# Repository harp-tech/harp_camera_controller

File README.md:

# Harp Camera Controlelr

This device contains the necessary circuitry to synchronously control and supply 2 cameras.

# Licensing

The code, designs, documentation, and photos available in this repository is free: you can redistribute it and/or modify it under the terms of the used license.
Each subdirectory will contain a license or, possibly, a set of licenses if it involves both hardware and software. Check files named LICENSE.

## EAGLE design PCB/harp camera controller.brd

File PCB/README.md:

# Harp Camera Controller

## Licensing

The designs, documentation, and photos available in this repository are free: you can redistribute it and/or modify it under the terms of the used license.
Check file named LICENSE.

Copyright OEPS 2021-2022

<br />This work is licensed under a <a rel="license" href="http://creativecommons.org/licenses/by-nc-sa/3.0/igo/">Creative Commons Attribution-NonCommercial-ShareAlike 3.0 IGO License</a>.

If your are interested in obtaining a license to sell this device, please contact info@oeps.tech

[1]: https://docs.google.com/spreadsheets/d/1aobmmEzBDethzIlrm1eg0eYkBqlyX3s9WbA9KgRwVQI/edit?usp=sharing

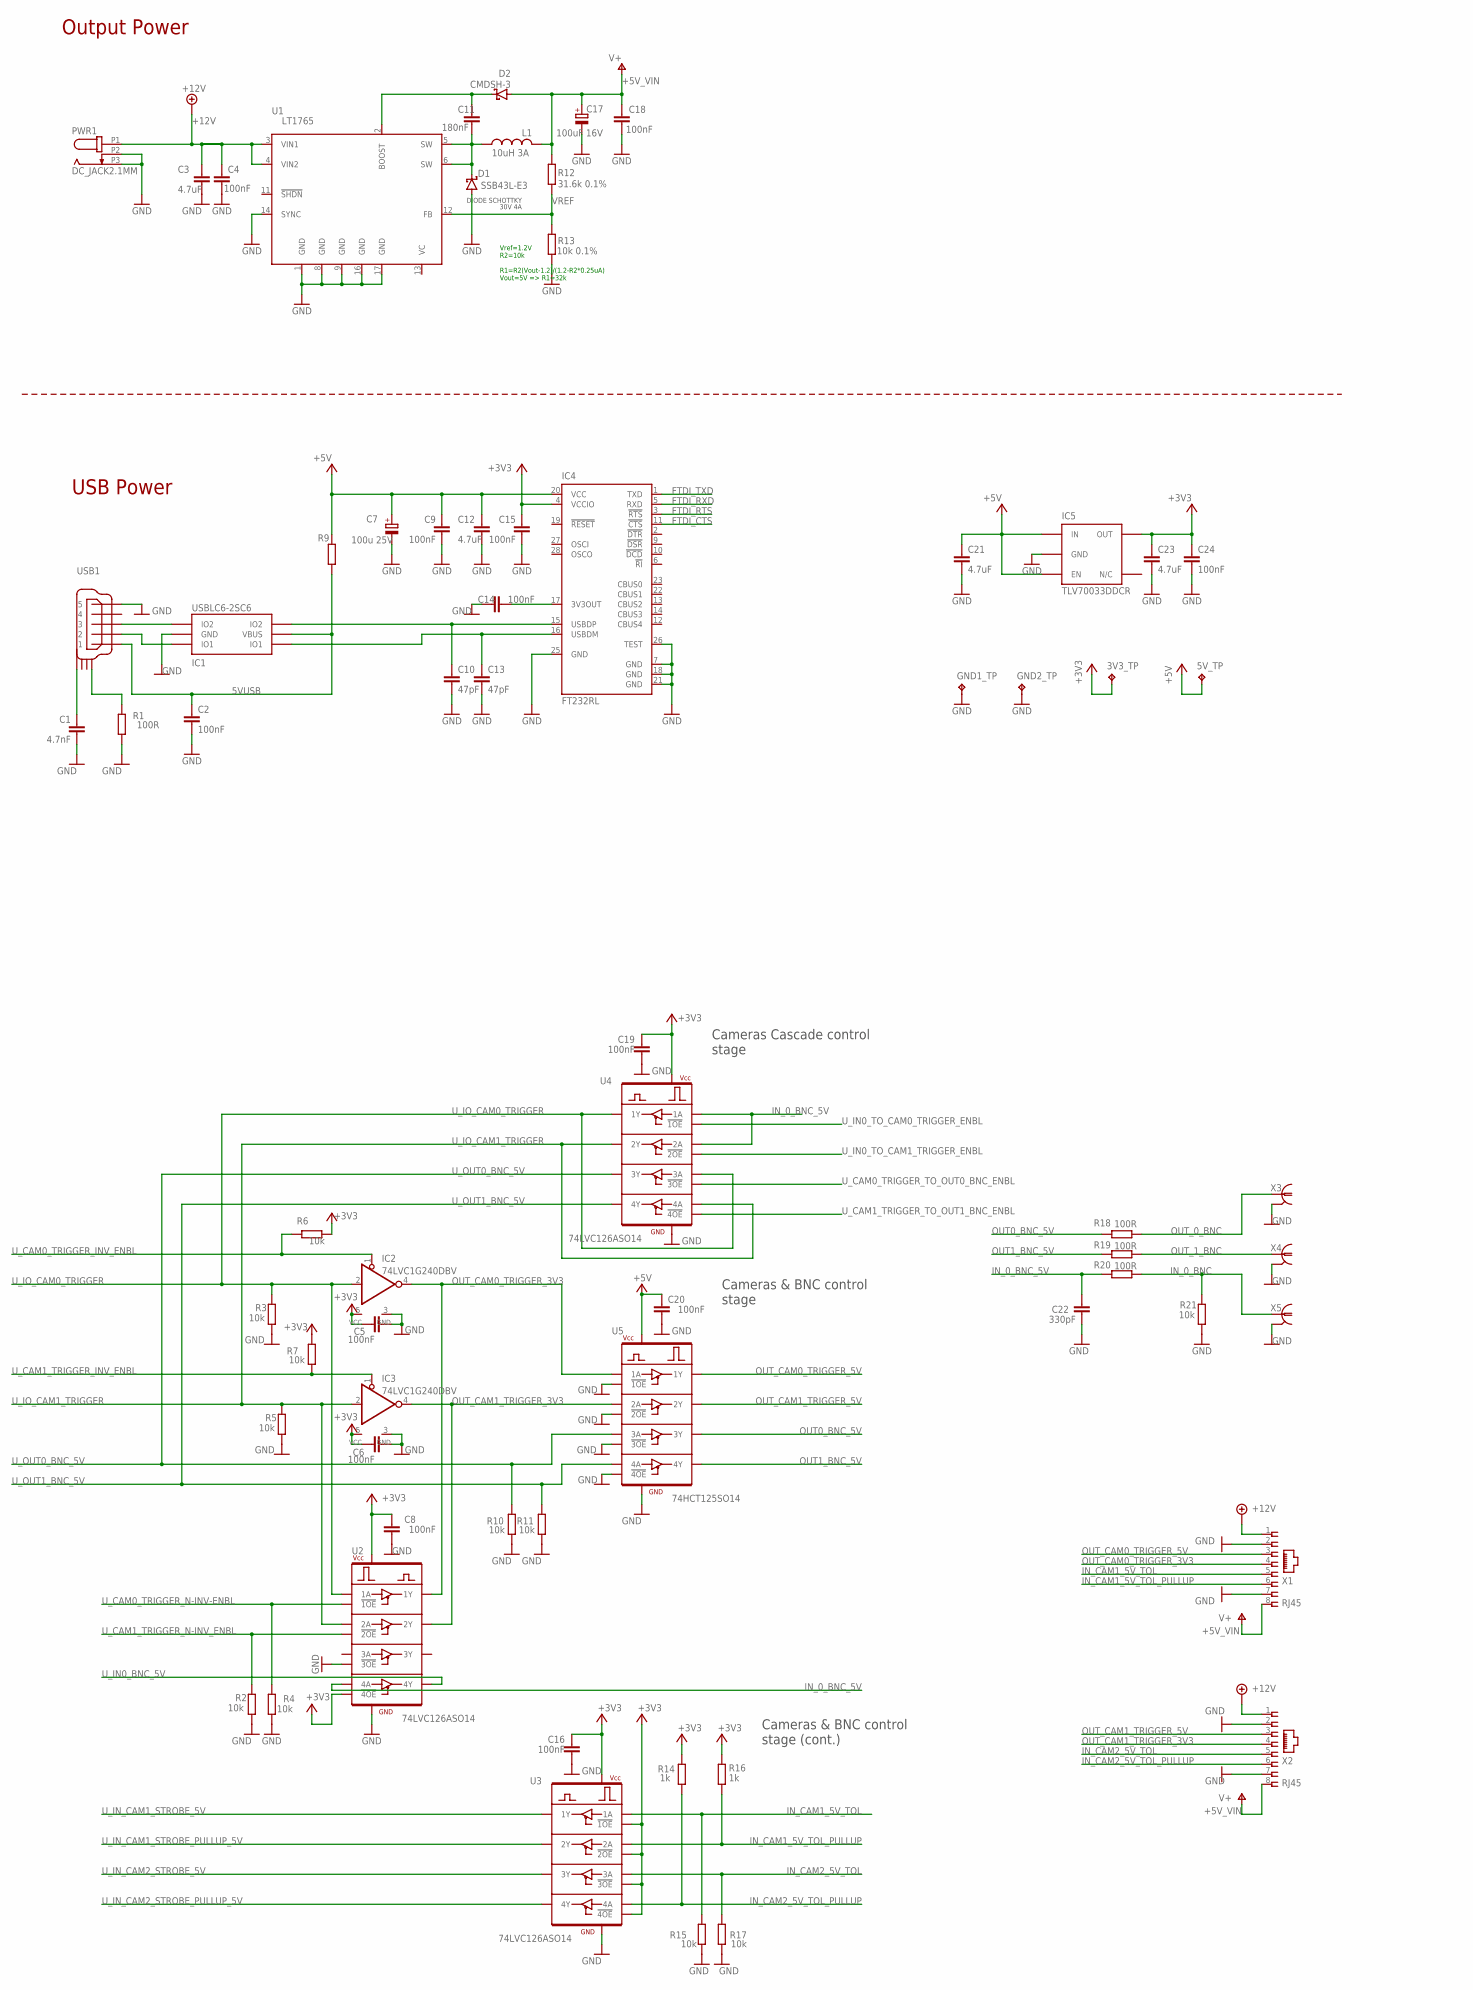
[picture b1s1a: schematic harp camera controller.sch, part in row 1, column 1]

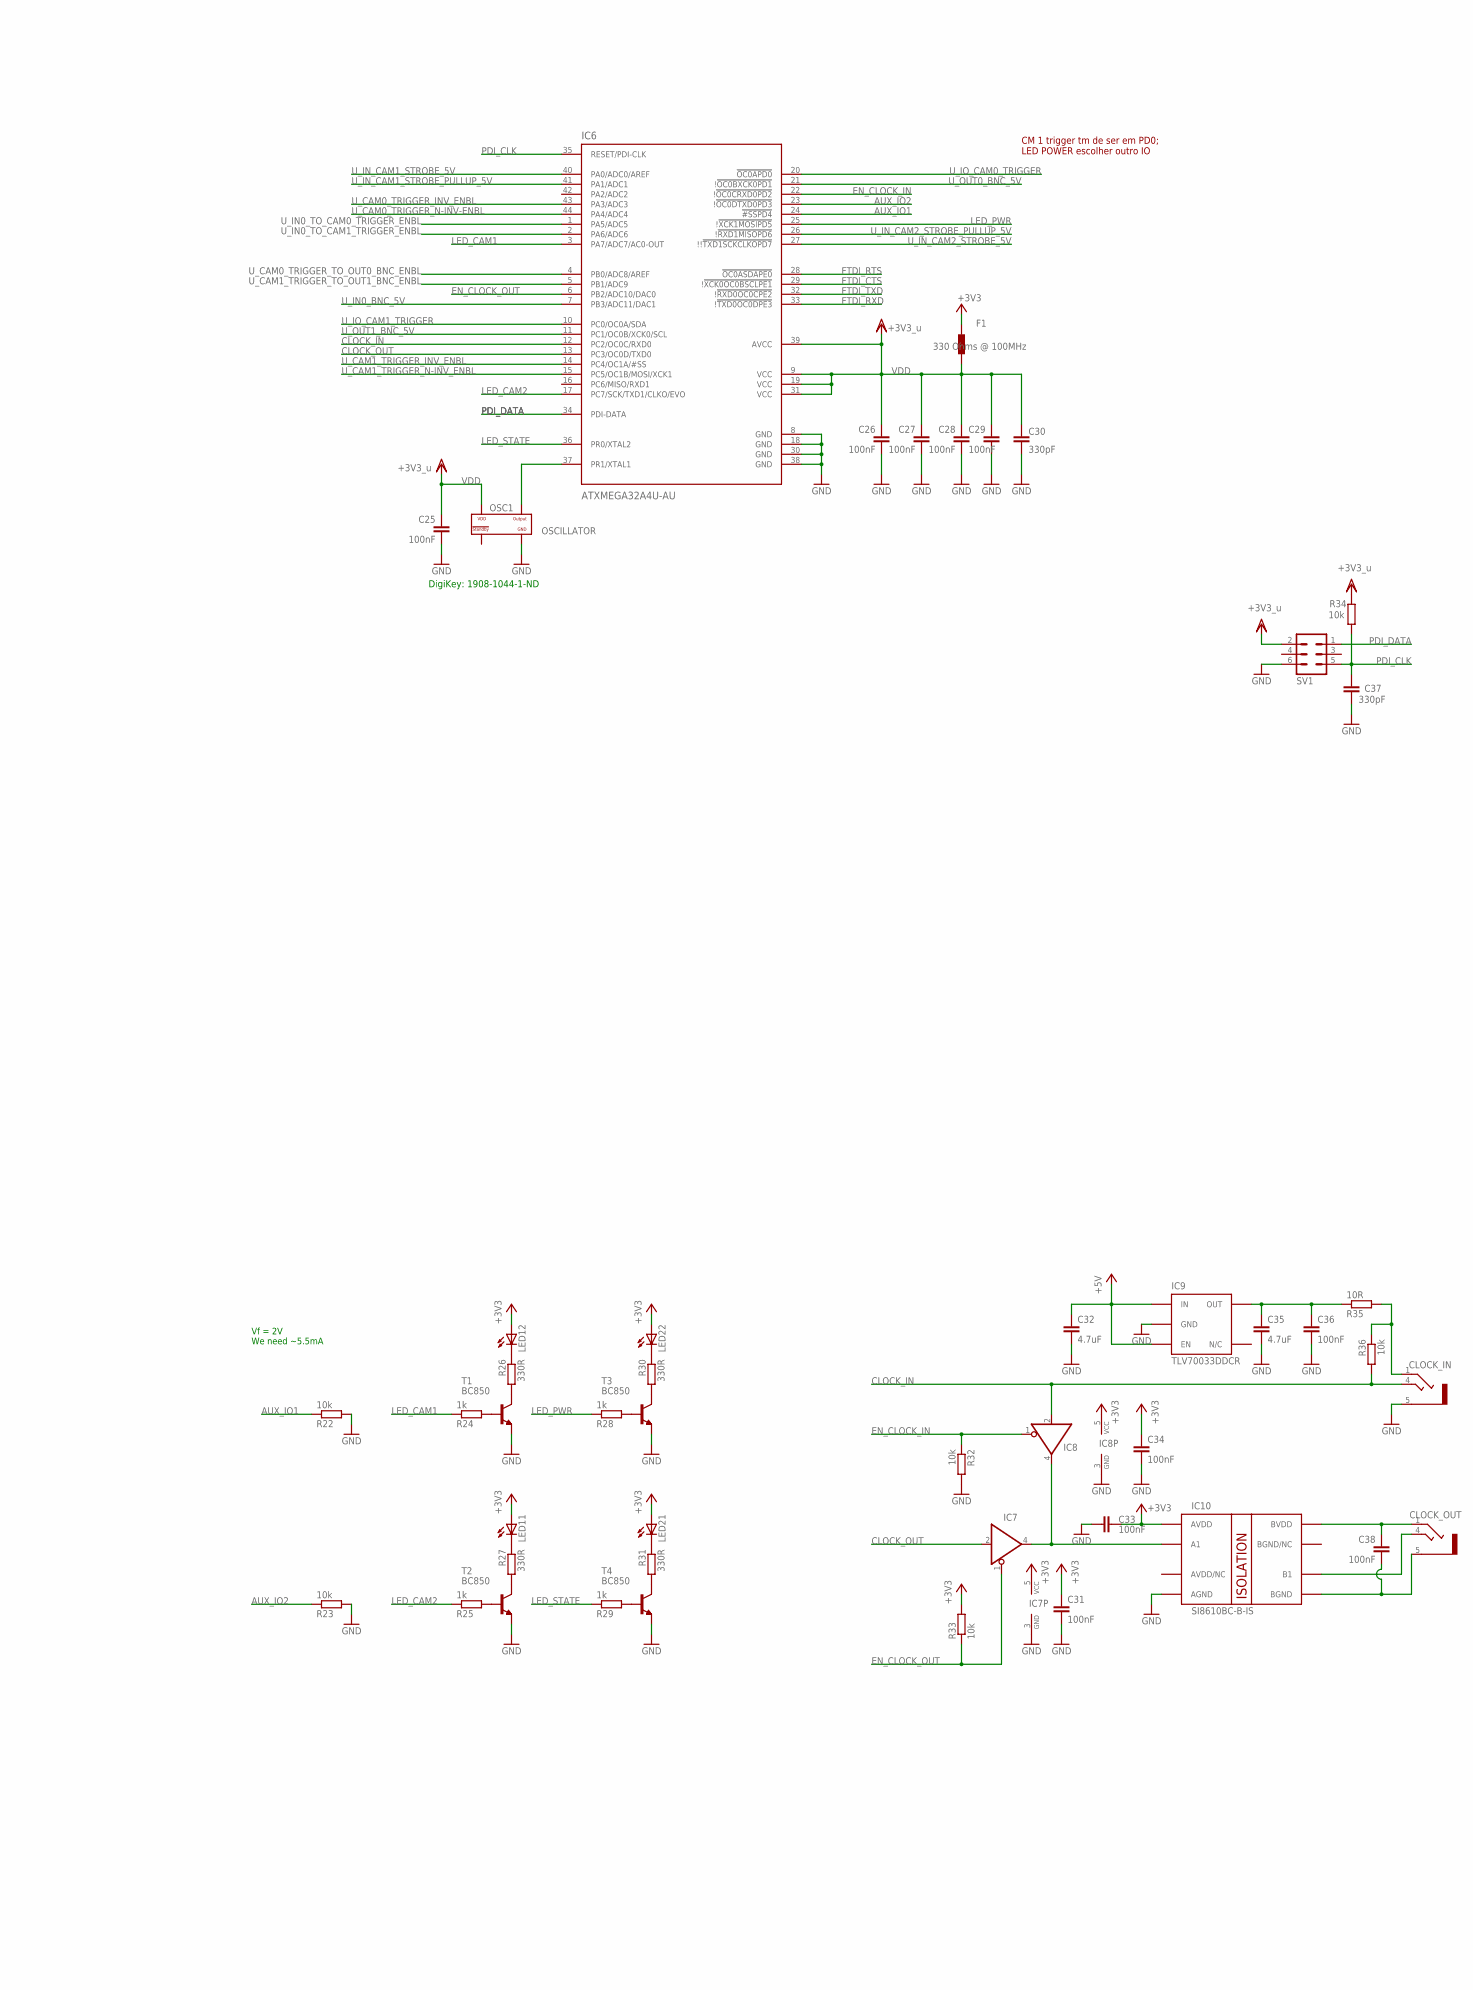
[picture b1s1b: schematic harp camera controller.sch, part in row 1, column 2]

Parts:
3V3_TP, 5V_TP: TPPAD1-13; P1-13; MOUSER_PN N.A.; DIGIKEY_PN N.A.
C1: 4.7nF; C0402; MPN 885012205084; DIGIKEY_PN 732-12234-1-ND
C2, C4, C5, C6, C8, C9, C14, C15, C16, C18, C19, C20, C24, C25, C26, C27, C28, C29, C31, C33, C34, C36, C38: 100nF; C0402; MPN C1005X7R1H104K050BB; DIGIKEY_PN 445-5932-1-ND
C3: 4.7uF; C0805; MPN CL21A475KLCLQNC; DIGIKEY_PN 1276-6722-1-ND
C7: 100u 25V; TT2D6; MPN EEU-FM1E101B; DIGIKEY_PN P19702CT-ND
C10, C13: 47pF; C0402; MPN 04025A470JAT2A; DIGIKEY_PN 478-1078-1-ND
C11: 180nF; C0603; MPN GCG188R91H184KA01D; DIGIKEY_PN 490-GCG188R91H184KA01DCT-ND
C12, C21, C23, C32, C35: 4.7uF; C0603; MPN C1608X6S1C475K080AC; DIGIKEY_PN 445-9118-1-ND
C17: 100uF 16V; CT7343; MPN T491D107K016AT7280; DIGIKEY_PN 399-18066-1-ND
C22, C30, C37: 330pF; C0402; MPN C0402C331J5GACTU; DIGIKEY_PN 399-7787-1-ND
CLOCK_IN: CLCK_JACK; 35RASMT2BHNTRX; MOUSER_PN 502-35RASMT2BHNTRX; DIGIKEY_PN SC1489-1-ND
CLOCK_OUT: CLCK_JACK; 35RASMT2BHNTRX; MOUSER_PN 502-35RASMT2BHNTRX; DIGIKEY_PN SC1489-1-ND
D1: SSB43L-E3; SMB; MOUSER_PN 625-SSB43L-E3; DIGIKEY_PN SSB43L-E3/52TGICT-ND
D2: CMDSH-3; SOD323-R; MOUSER_PN 610-CMDSH-3; DIGIKEY_PN 1514-CMDSH-3TRPBFREECT-ND
F1: 330 Ohms @ 100MHz; R0603; MOUSER_PN 81-BLM18SG331TN1D; DIGIKEY_PN 490-3997-1-ND
GND1_TP, GND2_TP: TPPAD1-13; P1-13; MOUSER_PN N.A.; DIGIKEY_PN N.A.
IC1: USBLC6-2SC6; SOT23-6L; MOUSER_PN 511-USBLC6-2SC6; DIGIKEY_PN 497-5235-1-ND
IC2, IC3: 74LVC1G240DBV; SOT23-5; MOUSER_PN 595-SN74LVC1G240DBVR; DIGIKEY_PN 296-11609-1-ND
IC4: FT232RL; SSOP28; MOUSER_PN 895-FT232RL; DIGIKEY_PN 768-1007-1-ND
IC5, IC9: TLV70033DDCR; TSOT23-5; MOUSER_PN 595-TLV70033DDCR; DIGIKEY_PN 296-27937-1-ND
IC6: ATXMEGA32A4U-AU; QFP80P1200X1200X120-44N; MOUSER_PN 556-ATXMEGA32A4U-AU; DIGIKEY_PN ATXMEGA32A4U-AURCT-ND
IC7, IC8: SN74LVC1G125DBVT; SOT23-5; MOUSER_PN 595-SN74LVC1G125DBVT; DIGIKEY_PN 296-26595-1-ND
IC10: SI8610BC-B-IS; SO-08; MOUSER_PN 634-SI8610EC-B-IS; DIGIKEY_PN 336-2058-5-ND
L1: 10uH 3A; L_IHLP_PADS; MOUSER_PN 70-IHLP2525CZER100M0; DIGIKEY_PN 541-1013-2-ND
LED1, LED2: RED_LEDs; 569-011X-X00_LED_ARRAY; MOUSER_PN 645-569-0111-100F; DIGIKEY_PN 350-1782-ND
OSC1: OSCILLATOR; OSCILLATOR_3.2X2.5; MOUSER_PN N.A. - ALTERNATIVE ONLY; DIGIKEY_PN 1908-1044-1-ND
PWR1: DC_JACK2.1MM; DC_POWER_INPUT_2.1MM; MOUSER_PN 163-179PH; DIGIKEY_PN DIGIKEY N.A.
R1, R18, R19, R20: 100R; R0603; MPN ERJ-3EKF1000V; DIGIKEY_PN P100HCT-ND
R2, R3, R4, R5, R6, R7, R10, R11, R15, R17, R21, R22, R23, R32, R33, R34, R36: 10k; R0402; MPN CRCW040210K0FKED; DIGIKEY_PN 541-3959-1-ND
R9: 40R@100MHz; R0805; MPN MI0805K400R-10; DIGIKEY_PN 240-2389-1-ND
R12: 31.6k 0.1%; R0402; MPN RC0402FR-0740K2L; DIGIKEY_PN 311-40.2KLRCT-ND
R13: 10k 0.1%; R0402; MPN CRCW040210K0FKED; DIGIKEY_PN 541-3959-1-ND
R14, R16, R24, R25, R28, R29: 1k; R0402; MPN CRCW04021K00FKEDC; DIGIKEY_PN 541-3961-1-ND
R26, R27, R30, R31: 330R; R0402; MPN RC0402FR-07330RL; DIGIKEY_PN 311-330LRCT-ND
R35: 10R; R0402; MPN CRCW040210R0FKEDC; DIGIKEY_PN 541-3964-2-ND
SV1: PROG HEADER; MA03-2; MOUSER_PN 710-61300621121; DIGIKEY_PN 732-5295-ND
T1, T2, T3, T4: BC850; SOT23; MOUSER_PN 771-BC850C-T/R; DIGIKEY_PN 1727-4862-1-ND
U1: LT1765; TSSOP16EXP; MOUSER_PN 584-LT1765EFE#TRPBF; DIGIKEY_PN LT1765EFE#PBF-ND
U2, U3, U4: 74LVC126ASO14; SO14; MOUSER_PN 771-LVC126AD118; DIGIKEY_PN 1727-6365-1-ND
U5: 74HCT125SO14; SO14; MOUSER_PN 771-74HCT125D-T; DIGIKEY_PN 1727-2834-1-ND
USB1: mini USB; 240-0002-1; MOUSER_PN 798-UX60-MB-5S8; DIGIKEY_PN H2960TR-ND
X1, X2: RJ45; RJ45-NO-SHIELD; MOUSER_PN 571-2158771; DIGIKEY_PN A105009CT-ND
X3, X4, X5: BNC plug; 0731000105; MOUSER_PN N.A.; DIGIKEY_PN WM5524-ND

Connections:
5VUSB: C2.1, IC1.P$5 (VBUS), R9.2, USB1.P$1 (1)
+3V3: 3V3_TP.TP, C5.1, C6.1, C8.1, C15.1, C16.1, C19.1, C23.1, C24.1, C31.1, C33.1, C34.1, F1.2, IC2.5 (VCC), IC3.5 (VCC), IC4.4 (VCCIO), IC5.5 (OUT), IC7.5 (VCC), IC8.5 (VCC), IC10.1 (AVDD), LED1.A1 (A), LED1.A2 (A), LED2.A1 (A), LED2.A2 (A), R6.1, R7.1, R14.1, R16.1, R33.2, U2.13 (!4OE), U2.14 (VCC), U3.1 (!1OE), U3.4 (!2OE), U3.10 (!3OE), U3.13 (!4OE), U3.14 (VCC), U4.14 (VCC)
+5V: 5V_TP.TP, C7.+, C9.1, C12.1, C20.1, C21.1, C32.1, IC4.20 (VCC), IC5.1 (IN), IC5.3 (EN), IC9.1 (IN), IC9.3 (EN), R9.1, U5.14 (VCC)
+5V_VIN: C17.+, C18.1, D2.A, L1.1, R12.2, X1.8, X2.8
+12V: C3.1, C4.1, PWR1.P1 (1), U1.3 (VIN1), U1.4 (VIN2), X1.1, X2.1
AUX_IO1: IC6.24 (!#SSPD4), R22.1
AUX_IO2: IC6.23 (!!OC0DTXD0PD3), R23.1
CLOCK_IN: CLOCK_IN.4, IC6.12 (PC2/OC0C/RXD0), IC8.2 (I), R36.2
CLOCK_OUT: IC6.13 (PC3/OC0D/TXD0), IC7.2 (I)
EN_CLOCK_IN: IC6.22 (!!OC0CRXD0PD2), IC8.1 (OE), R32.1
EN_CLOCK_OUT: IC6.6 (PB2/ADC10/DAC0), IC7.1 (OE), R33.1
FTDI_CTS: IC4.11 (!CTS), IC6.29 (!!XCK0OC0BSCLPE1)
FTDI_RTS: IC4.3 (!RTS), IC6.28 (!OC0ASDAPE0)
FTDI_RXD: IC4.5 (RXD), IC6.33 (!!TXD0OC0DPE3)
FTDI_TXD: IC4.1 (TXD), IC6.32 (!!RXD0OC0CPE2)
GND: C1.2, C2.2, C3.2, C4.2, C5.2, C6.2, C7.-, C8.2, C9.2, C10.2, C12.2, C13.2, C14.2, C15.2, C16.2, C17.-, C18.2, C19.2, C20.2, C21.2, C22.2, C23.2, C24.2, C25.2, C26.2, C27.2, C28.2, C29.2, C30.2, C31.2, C32.2, C33.2, C34.2, C35.2, C36.2, C37.2, CLOCK_IN.5, D1.A, GND1_TP.TP, GND2_TP.TP, IC1.P$2 (GND), IC2.3 (GND), IC3.3 (GND), IC4.7 (GND), IC4.18 (GND), IC4.21 (GND), IC4.25 (GND), IC4.26 (TEST), IC5.2 (GND), IC6.8 (GND), IC6.18 (GND), IC6.30 (GND), IC6.38 (GND), IC7.3 (GND), IC8.3 (GND), IC9.2 (GND), IC10.4 (AGND), OSC1.P$2 (GND), PWR1.P2 (2), PWR1.P3 (3), R1.2, R2.1, R3.1, R4.1, R5.1, R10.2, R11.2, R13.1, R15.1, R17.1, R21.1, R22.2, R23.2, R32.2, SV1.6, T1.2 (E), T2.2 (E), T3.2 (E), T4.2 (E), U1.1 (GND), U1.8 (GND), U1.9 (GND), U1.14 (SYNC), U1.16 (GND), U1.17 (GND), U2.7 (GND), U2.10 (!3OE), U3.7 (GND), U4.7 (GND), U5.1 (!1OE), U5.4 (!2OE), U5.7 (GND), U5.10 (!3OE), U5.13 (!4OE), USB1.P$5 (5), X1.2, X1.7, X2.2, X2.7, X3.2, X3.3 (2), X4.2, X4.3 (2), X5.2, X5.3 (2)
GND_ISO: C38.2, CLOCK_OUT.5, IC10.5 (BGND)
IN_0_BNC: R20.1, R21.2, X5.1
IN_0_BNC_5V: C22.1, R20.2, U2.12 (4A), U4.2 (1A), U4.5 (2A)
IN_CAM1_5V_TOL: R15.2, U3.2 (1A), X1.5
IN_CAM1_5V_TOL_PULLUP: R16.2, U3.5 (2A), X1.6
IN_CAM2_5V_TOL: R17.2, U3.9 (3A), X2.5
IN_CAM2_5V_TOL_PULLUP: R14.2, U3.12 (4A), X2.6
LED_CAM1: IC6.3 (PA7/ADC7/AC0-OUT), R24.1
LED_CAM2: IC6.17 (PC7/SCK/TXD1/CLKO/EVO), R25.1
LED_PWR: IC6.25 (!!XCK1MOSIPD5), R28.1
LED_STATE: IC6.36 (PR0/XTAL2), R29.1
unnamed: R24.2, T1.1 (B)
unnamed: CLOCK_OUT.4, IC10.6 (B1)
unnamed: C38.1, CLOCK_OUT.1, IC10.8 (BVDD)
unnamed: R26.2, T1.3 (C)
unnamed: C11.2, D1.C, L1.2, U1.5 (SW), U1.6 (SW)
unnamed: C11.1, D2.C, U1.2 (BOOST)
unnamed: R25.2, T2.1 (B)
unnamed: C14.1, IC4.17 (3V3OUT)
unnamed: IC1.P$1 (IO1), USB1.P$2 (2)
unnamed: CLOCK_IN.1, R35.2, R36.1
unnamed: C35.1, C36.1, IC9.5 (OUT), R35.1
unnamed: IC7.4 (O), IC8.4 (O), IC10.2 (A1)
unnamed: R27.2, T2.3 (C)
unnamed: IC1.P$3 (IO2), USB1.P$3 (3)
unnamed: R28.2, T3.1 (B)
unnamed: R30.2, T3.3 (C)
unnamed: R29.2, T4.1 (B)
unnamed: C1.1, USB1.SHIELD_4
unnamed: R31.2, T4.3 (C)
unnamed: R1.1, USB1.SHIELD_1
unnamed: LED2.C1 (C), R31.1
unnamed: LED2.C2 (C), R30.1
unnamed: LED1.C2 (C), R26.1
unnamed: LED1.C1 (C), R27.1
OSC2: IC6.37 (PR1/XTAL1), OSC1.P$3 (OUTPUT)
OUT0_BNC_5V: R18.2, U5.8 (3Y)
OUT1_BNC_5V: R19.2, U5.11 (4Y)
OUT_0_BNC: R18.1, X3.1
OUT_1_BNC: R19.1, X4.1
OUT_CAM0_TRIGGER_3V3: IC2.4 (O), U2.3 (1Y), U5.2 (1A), X1.4
OUT_CAM0_TRIGGER_5V: U5.3 (1Y), X1.3
OUT_CAM1_TRIGGER_3V3: IC3.4 (O), U2.6 (2Y), U5.5 (2A), X2.4
OUT_CAM1_TRIGGER_5V: U5.6 (2Y), X2.3
PDI_CLK: C37.1, IC6.35 (RESET/PDI-CLK), R34.1, SV1.5
PDI_DATA: IC6.34 (PDI-DATA), SV1.1
USBDM: C13.1, IC1.P$6 (IO1), IC4.16 (USBDM)
USBDP: C10.1, IC1.P$4 (IO2), IC4.15 (USBDP)
U_CAM0_TRIGGER_INV_ENBL: IC2.1 (OE), IC6.43 (PA3/ADC3), R6.2
U_CAM0_TRIGGER_N-INV-ENBL: IC6.44 (PA4/ADC4), R4.2, U2.1 (!1OE)
U_CAM0_TRIGGER_TO_OUT0_BNC_ENBL: IC6.4 (PB0/ADC8/AREF), U4.10 (!3OE)
U_CAM1_TRIGGER_INV_ENBL: IC3.1 (OE), IC6.14 (PC4/OC1A/#SS), R7.2
U_CAM1_TRIGGER_N-INV_ENBL: IC6.15 (PC5/OC1B/MOSI/XCK1), R2.2, U2.4 (!2OE)
U_CAM1_TRIGGER_TO_OUT1_BNC_ENBL: IC6.5 (PB1/ADC9), U4.13 (!4OE)
U_IN0_BNC_5V: IC6.7 (PB3/ADC11/DAC1), U2.11 (4Y)
U_IN0_TO_CAM0_TRIGGER_ENBL: IC6.1 (PA5/ADC5), U4.1 (!1OE)
U_IN0_TO_CAM1_TRIGGER_ENBL: IC6.2 (PA6/ADC6), U4.4 (!2OE)
U_IN_CAM1_STROBE_5V: IC6.40 (PA0/ADC0/AREF), U3.3 (1Y)
U_IN_CAM1_STROBE_PULLUP_5V: IC6.41 (PA1/ADC1), U3.6 (2Y)
U_IN_CAM2_STROBE_5V: IC6.27 (!!!TXD1SCKCLKOPD7), U3.8 (3Y)
U_IN_CAM2_STROBE_PULLUP_5V: IC6.26 (!!RXD1MISOPD6), U3.11 (4Y)
U_IO_CAM0_TRIGGER: IC2.2 (I), IC6.20 (!OC0APD0), R3.2, U2.2 (1A), U4.3 (1Y), U4.9 (3A)
U_IO_CAM1_TRIGGER: IC3.2 (I), IC6.10 (PC0/OC0A/SDA), R5.2, U2.5 (2A), U4.6 (2Y), U4.12 (4A)
U_OUT0_BNC_5V: IC6.21 (!!OC0BXCK0PD1), R10.1, U4.8 (3Y), U5.9 (3A)
U_OUT1_BNC_5V: IC6.11 (PC1/OC0B/XCK0/SCL), R11.1, U4.11 (4Y), U5.12 (4A)
VDD: C25.1, C26.1, C27.1, C28.1, C29.1, C30.1, F1.1, IC6.9 (VCC), IC6.19 (VCC), IC6.31 (VCC), IC6.39 (AVCC), OSC1.P$4 (VDD), R34.2, SV1.2
VREF: R12.1, R13.2, U1.12 (FB)

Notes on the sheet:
Vf = 2V We need ~5.5mA
DigiKey: 1908-1044-1-ND
Vref=1.2V R2=10k R1=R2(Vout-1.2)/(1.2-R2*0.25uA) Vout=5V => R1=32k
DIODE SCHOTTKY 30V 4A
Output Power
USB Power
CM 1 trigger tm de ser em PD0; LED POWER escolher outro IO
Cameras & BNC control stage (cont.)
Cameras Cascade control stage
Cameras & BNC control stage

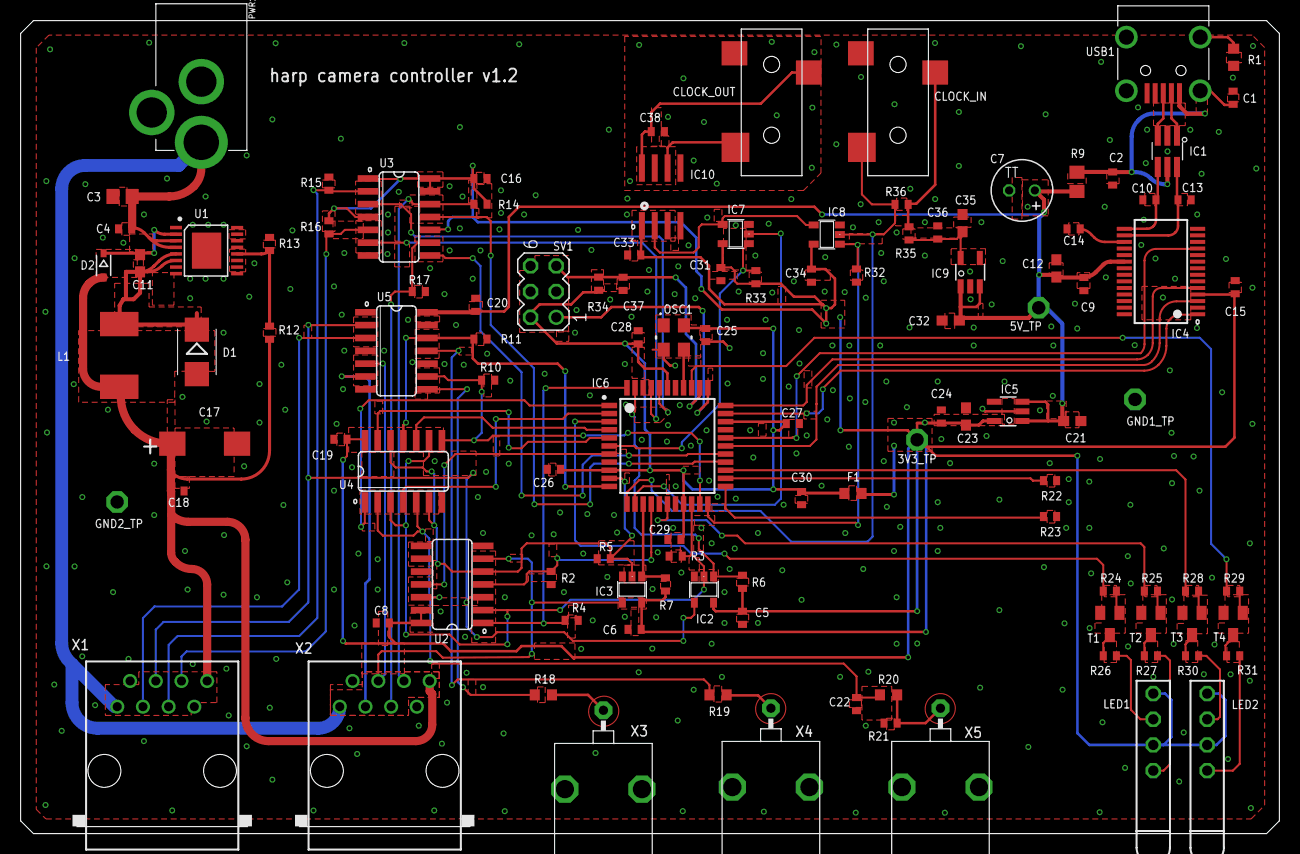
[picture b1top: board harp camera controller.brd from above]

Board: 2 copper layers, 124.5 x 80.4 mm, 113 parts (0 on the bottom side), 83 nets.

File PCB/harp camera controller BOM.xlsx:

Qty | Value | Package | Parts | MPN | Type
PCB COMPONENTS
2 | SN74LVC1G125DBVT | SOT23-5 | IC7, IC8 | SN74LVC1G125DBVT | SMD | -
1 | 74HCT125SO14 | SO14 | U5 | 74HCT125D,653 | SMD | -
3 | 74LVC126ASO14 | SO14 | U2, U3, U4 | 74LVC126AD,118 | SMD | -
2 | 74LVC1G240DBV | SOT23-5 | IC2, IC3 | SN74LVC1G240DBVR | SMD | -
1 | ATXMEGA32A4U-AU | QFP80P1200X1200X120-44N | IC6 | ATXMEGA32A4U-AUR | SMD | -
4 | BC850 | SOT23 | T1, T2, T3, T4 | BC850C,215 | SMD | -
1 | 330 Ohms @ 100MHz | R0603 | F1 | BLM18SG331TN1D | SMD | -
3 | BNC plug | 0731000105 | X3, X4, X5 | 73100-0105 | TH | -
23 | 100nF | C0402 | C2, C4, C5, C6, C8, C9, C14, C15, C16, C18, C19, C20, C24, C25, C26, C27, C28, 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 | C1005X7R1H104K050BB | SMD | -
3 | 330pF | C0402 | C22, C30, C37 | C0402C331J5GACTU | SMD | -
1 | 4.7nF | C0402 | C1 | 885012205084 | SMD | -
2 | 47pF | C0402 | C10, C13 | 04025A470JAT2A | SMD | -
1 | 180nF | C0603 | C11 | GCG188R91H184KA01D | SMD
5 | 4.7uF | C0603 | C12, C21, C23, C32, C35 | C1608X6S1C475K080AC | SMD | -
1 | 4.7uF | C0805 | C3 | CL21A475KLCLQNC | SMD
1 | 100uF 16V | CT7343 | C17 | T491D107K016AT7280 | SMD
1 | 100u 25V | TT2D6 | C7 | EEU-FM1E101B | SMD | -
1 | DC_JACK2.1MM | DC_POWER_INPUT_2.1MM | PWR1 | 163-179PH-EX | TH | -
1 | FT232RL | SSOP28 | IC4 | FT232RL-REEL | SMD | -
1 | 10uH 3A | L_IHLP_PADS | L1 | IHLP2525CZER100M01 | SMD
2 | RED_LEDs | 569-011X-X00_LED_ARRAY | LED1, LED2 | 5690-111-100F | TH | -
1 | LT1765 | TSSOP16EXP | U1 | LT1765EFE#PBF | SMD | -
1 | PROG HEADER | MA03-2 | SV1 | 61300621121 | TH | -
1 | OSCILLATOR | OSCILLATOR_3.2X2.5 | OSC1 | O 32,0-JT32C-A-K-3,3-LF | SMD | ALTERNATIVE: DSC1001CI5-032.0000
1 | 10R | R0402 | R35 | CRCW040210R0FKEDC | SMD | -
18 | 10k | R0402 | R2, R3, R4, R5, R6, R7, R8, R10, R11, R15, R17, R21, R22, R23, R32, R33, R34, R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 | CRCW040210K0FKED | SMD | -
1 | 10k 0.1% | R0402 | R13 | CPF0402B10KE1 | SMD | -
6 | 1k | R0402 | R14, R16, R24, R25, R28, R29 | CRCW04021K00FKEDC | SMD | -
1 | 34k 0.1% | R0402 | R12 | ERA2AEB3402X | SMD
4 | 330R | R0402 | R26, R27, R30, R31 | RC0402FR-07330RL | SMD | -
4 | 100R | R0603 | R1, R18, R19, R20 | ERJ-3EKF1000V | SMD | -
1 | 40R@100MHz | R0805 | R9 | MI0805K400R-10 | SMD | -
2 | RJ45 | RJ45-NO-SHIELD | X1, X2 | 215877-1 | TH | -
1 | SSB43L-E3 | SMB | D1 | SSB43L-E3/52T | SMD | -
1 | CMDSH-3 | SOD323-R | D2 | CMDSH-3 | SMD | -
1 | SI8610BC-B-IS | SO-08 | IC10 | SI8610EC-B-IS | SMD | ALTERNATIVE: ADUM110N0BRZ
2 | CLCK_JACK | 35RASMT2BHNTRX | CLOCK_IN, CLOCK_OUT | 35RASMT2BHNTRX | SMD | -
2 | TLV70033DDCR | TSOT23-5 | IC5, IC9 | TLV70033DDCR | SMD | SIMILAR & AVAILABLE = LP5951MFX-3.3/NOPB >> DIGIKEY_PN: 296-47807-2-ND MOUSER_P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
1 | mini USB | 240-0002-1 | USB1 | UX60-MB-5S8 | SMD | END OF LIFE COMPONENT BY SEPTEMBER 2021
1 | USBLC6-2SC6 | SOT23-6L | IC1 | USBLC6-2SC6 | SMD | EQUIVALENT: RCLAMP0504S.TCT
POST-PRODUCTION
1 |  |  | Front Panel PCB | PCBWAY
1 |  |  | Rear Panel PCB | PCBWAY
1 |  |  | Enclosure | B5-080BK
4 |  |  | Bumper Cylindrical Dome 9.53mm | SJ-5306-CLEAR-3000/CASE
ACCESSORIES
1 |  |  | 3.5mm stereo jack cable 1.2 m, Black | AV13646
1 |  |  | 0.9 left angle USB cable | USB2HABM3RA
NOTES
 |  |  |  | Number of unique parts | 39
 |  |  |  | Number of unique SMD parts | 34
 |  |  |  | Number of unique TH parts | 5
 |  |  |  | Number of SMD parts | 101
 |  |  |  | Number of TH parts | 9
 |  | Optional
 |  | Holder: MF80BK2

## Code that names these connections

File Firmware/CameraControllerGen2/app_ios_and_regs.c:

#include <avr/io.h>
#include "hwbp_core_types.h"
#include "app_ios_and_regs.h"

/************************************************************************/
/* Configure and initialize IOs                                         */
/************************************************************************/
void init_ios(void)
{	/* Configure input pins */
	io_pin2in(&PORTA, 0, PULL_IO_TRISTATE, SENSE_IO_EDGES_BOTH);         // CAM0_STROBE
	io_pin2in(&PORTA, 1, PULL_IO_TRISTATE, SENSE_IO_EDGES_BOTH);         // CAM0_STROBE_PU
	io_pin2in(&PORTD, 7, PULL_IO_TRISTATE, SENSE_IO_EDGES_BOTH);         // CAM1_STROBE
	io_pin2in(&PORTD, 6, PULL_IO_TRISTATE, SENSE_IO_EDGES_BOTH);         // CAM1_STROBE_PU
	io_pin2in(&PORTB, 3, PULL_IO_TRISTATE, SENSE_IO_EDGES_BOTH);         // INPUT0
	io_pin2in(&PORTD, 0, PULL_IO_TRISTATE, SENSE_IO_EDGE_RISING);        // CAM0
	io_pin2in(&PORTD, 1, PULL_IO_TRISTATE, SENSE_IO_NO_INT_USED);        // OUT0
	io_pin2in(&PORTC, 0, PULL_IO_TRISTATE, SENSE_IO_EDGE_RISING);        // CAM1
	io_pin2in(&PORTC, 1, PULL_IO_TRISTATE, SENSE_IO_NO_INT_USED);        // OUT1

	/* Configure input interrupts */
	io_set_int(&PORTA, INT_LEVEL_LOW, 0, (1<<0), false);                 // CAM0_STROBE
	io_set_int(&PORTA, INT_LEVEL_LOW, 0, (1<<1), false);                 // CAM0_STROBE_PU
	io_set_int(&PORTD, INT_LEVEL_LOW, 0, (1<<7), false);                 // CAM1_STROBE
	io_set_int(&PORTD, INT_LEVEL_LOW, 0, (1<<6), false);                 // CAM1_STROBE_PU
	io_set_int(&PORTB, INT_LEVEL_LOW, 1, (1<<3), false);                 // INPUT0
	io_set_int(&PORTD, INT_LEVEL_LOW, 1, (1<<0), false);                 // CAM0
	io_set_int(&PORTC, INT_LEVEL_LOW, 1, (1<<0), false);                 // CAM1

	/* Configure output pins */
	io_pin2out(&PORTA, 7, OUT_IO_DIGITAL, IN_EN_IO_EN);                  // LED_CAM0
	io_pin2out(&PORTC, 7, OUT_IO_DIGITAL, IN_EN_IO_EN);                  // LED_CAM1
	io_pin2out(&PORTR, 0, OUT_IO_DIGITAL, IN_EN_IO_EN);                  // LED_STATE
	io_pin2out(&PORTD, 5, OUT_IO_DIGITAL, IN_EN_IO_EN);                  // LED_PWR
	io_pin2out(&PORTA, 3, OUT_IO_DIGITAL, IN_EN_IO_EN);                  // EN_CAM0_TRIGGER_INV
	io_pin2out(&PORTA, 4, OUT_IO_DIGITAL, IN_EN_IO_EN);                  // EN_CAM0_TRIGGER_N_INV
	io_pin2out(&PORTC, 4, OUT_IO_DIGITAL, IN_EN_IO_EN);                  // EN_CAM1_TRIGGER_INV
	io_pin2out(&PORTC, 5, OUT_IO_DIGITAL, IN_EN_IO_EN);                  // EN_CAM1_TRIGGER_N_INV
	io_pin2out(&PORTB, 0, OUT_IO_DIGITAL, IN_EN_IO_EN);                  // EN_CAM0_TO_OUT0
	io_pin2out(&PORTB, 1, OUT_IO_DIGITAL, IN_EN_IO_EN);                  // EN_CAM1_TO_OUT1
	io_pin2out(&PORTA, 5, OUT_IO_DIGITAL, IN_EN_IO_EN);                  // EN_IN0_TO_CAM0
	io_pin2out(&PORTA, 6, OUT_IO_DIGITAL, IN_EN_IO_EN);                  // EN_IN0_TO_CAM1
	io_pin2out(&PORTD, 2, OUT_IO_DIGITAL, IN_EN_IO_EN);                  // EN_CLOCK_IN
	io_pin2out(&PORTB, 2, OUT_IO_DIGITAL, IN_EN_IO_EN);                  // EN_CLOCK_OUT

	/* Initialize output pins */
	clr_LED_CAM0;
	clr_LED_CAM1;
	clr_LED_STATE;
	clr_LED_PWR;
	clr_EN_CAM0_TRIGGER_INV;
	clr_EN_CAM0_TRIGGER_N_INV;
	clr_EN_CAM1_TRIGGER_INV;
	clr_EN_CAM1_TRIGGER_N_INV;
	clr_EN_CAM0_TO_OUT0;
	clr_EN_CAM1_TO_OUT1;
	clr_EN_IN0_TO_CAM0;
	clr_EN_IN0_TO_CAM1;
	set_EN_CLOCK_IN;
	clr_EN_CLOCK_OUT;
}

/************************************************************************/
/* Registers' stuff                                                     */
/************************************************************************/
AppRegs app_regs;

uint8_t app_regs_type[] = {
	TYPE_U8,
	TYPE_U8,
	TYPE_U8,
	TYPE_U8,
	TYPE_U8,
	TYPE_U8,
	TYPE_U32,
	TYPE_U32,
	TYPE_U8,
	TYPE_U8,
	TYPE_U8,
	TYPE_U8,
	TYPE_U8,
	TYPE_U16,
	TYPE_U16,
	TYPE_U8,
	TYPE_U8,
	TYPE_U8,
	TYPE_U8,
	TYPE_U8,
	TYPE_U16,
	TYPE_U16,
	TYPE_U8,
	TYPE_U8,
	TYPE_U8,
	TYPE_U8,
	TYPE_U8,
	TYPE_U8,
	TYPE_U8,
	TYPE_U8,
	TYPE_U8,
	TYPE_U8,
	TYPE_U8
};

uint16_t app_regs_n_elements[] = {
	1,
	1,
	1,
	1,
	1,
	1,
	1,
	1,
	1,
	1,
	1,
	1,
	1,
	1,
	1,
	1,
	1,
	1,
	1,
	1,
	1,
	1,
	1,
	1,
	1,
	1,
	1,
	1,
	1,
	1,
	1,
	1,
	1
};

uint8_t *app_regs_pointer[] = {
	(uint8_t*)(&app_regs.REG_CAM0_EVENT),
	(uint8_t*)(&app_regs.REG_CAM1_EVENT),
	(uint8_t*)(&app_regs.REG_CAM0_EVENT_CONFIG),
	(uint8_t*)(&app_regs.REG_CAM1_EVENT_CONFIG),
	(uint8_t*)(&app_regs.REG_START_AND_STOP),
	(uint8_t*)(&app_regs.REG_START_AND_STOP_TIMESTAMPED),
	(uint8_t*)(&app_regs.REG_START_TIMESTAMP),
	(uint8_t*)(&app_regs.REG_STOP_TIMESTAMP),
	(uint8_t*)(&app_regs.REG_RESERVED0),
	(uint8_t*)(&app_regs.REG_RESERVED1),
	(uint8_t*)(&app_regs.REG_CAM0_TRIGGER_CONFIG),
	(uint8_t*)(&app_regs.REG_CAM0_TRIGGER_INVERTED),
	(uint8_t*)(&app_regs.REG_CAM0_STROBE_SOURCE),
	(uint8_t*)(&app_regs.REG_CAM0_TRIGGER_FREQUENCY),
	(uint8_t*)(&app_regs.REG_CAM0_TRIGGER_DURATION_US),
	(uint8_t*)(&app_regs.REG_RESERVED2),
	(uint8_t*)(&app_regs.REG_RESERVED3),
	(uint8_t*)(&app_regs.REG_CAM1_TRIGGER_CONFIG),
	(uint8_t*)(&app_regs.REG_CAM1_TRIGGER_INVERTED),
	(uint8_t*)(&app_regs.REG_CAM1_STROBE_SOURCE),
	(uint8_t*)(&app_regs.REG_CAM1_TRIGGER_FREQUENCY),
	(uint8_t*)(&app_regs.REG_CAM1_TRIGGER_DURATION_US),
	(uint8_t*)(&app_regs.REG_RESERVED4),
	(uint8_t*)(&app_regs.REG_RESERVED5),
	(uint8_t*)(&app_regs.REG_OUT0_CONFIG),
	(uint8_t*)(&app_regs.REG_OUT1_CONFIG),
	(uint8_t*)(&app_regs.REG_RESERVED6),
	(uint8_t*)(&app_regs.REG_RESERVED7),
	(uint8_t*)(&app_regs.REG_OUT_SET),
	(uint8_t*)(&app_regs.REG_OUT_CLEAR),
	(uint8_t*)(&app_regs.REG_OUT_TOGGLE),
	(uint8_t*)(&app_regs.REG_OUT_WRITE),
	(uint8_t*)(&app_regs.REG_IN_STATE)
};

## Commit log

2021-11-05 First commit.
2021-11-29 First firmware commit.
2021-11-29 Updated PCB to version 1.1.
2022-03-25 Removed 80Hz default frequency.
2022-03-25 Corrected START and STOP commands.
2022-03-25 Added single frame command.
2022-03-25 Corrected visual enable/disable and catastrophic error handle.
2022-03-25 Improved strobe reading.
2022-03-25 Removed debug code and updated registers' default values,
2022-03-25 Increased firmware version and corrected minor bug.
2022-03-25 Corrected enable of buffers U2, U3, and U4.
2022-03-25 Minor corrections.
2022-03-26 Added rear and front panels.
2022-03-26 Added PCB gerbers.
2022-04-05 Updated read panel with a square hole for the 12V plug.
2022-04-10 Corrected PN of R12
2022-04-13 Updated PCB to version 1.2
2022-04-13 Added gerbers for PCB version 1.2
2022-04-13 Added camera controller breakout.
2022-04-13 Increased harp core to version 1.10
2022-04-13 Added a Bonsai workflow used for tests.
2022-05-02 Remapped CLKIN.
2022-05-08 Corrected bad STROBE remapping.
2022-05-08 Updated hardware version to match current PCB version.
2022-05-08 Changed library path to relative.
2022-05-08 Small updates on LICENSE and README.
2022-05-13 Changed 5V output to 5.3V and released PCB v1.2
2022-05-13 Released first firmware version.
2022-05-16 Added text to rear panel.
2022-07-08 Added new register START_AND_STOP_TIMESTAMPED.
2022-07-13 Implemented a new delayed start/stop register.
